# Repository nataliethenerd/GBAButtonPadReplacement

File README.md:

# GBA Button Pad Replacement

Open source replacement PCBs for the Game Boy Advance button contacts. Order as a flex PCB and solder to the test points (or traces if the test points are dead also). [Check out my GBA scans if you need help locating the traces](https://wiki.nataliethenerd.com/gameboy/gameboyadvance#agb-cpu-01)

## Follow me

If you are into Game Boy modding or retro gaming, please consider using code "NatalieTheNerd" at:

• [Retro Modding](http://RetroModding.com) 

• [Retro Game Repair Shop](http://RetroGameRepairShop.com) 

• [Extreme Rate](http://ExtremeRate.com)

**My socials**

• [Twitter](https://twitter.com/natalie_thenerd) 

• [BlueSky](https://bsky.app/profile/nataliethenerd.com) 

• [Instagram](https://www.instagram.com/natalie.thenerd/) 

• [Modded Gameboy Club](https://moddedgameboy.club/) - a club dedicated to the modification of Game Boys, freely sharing resources

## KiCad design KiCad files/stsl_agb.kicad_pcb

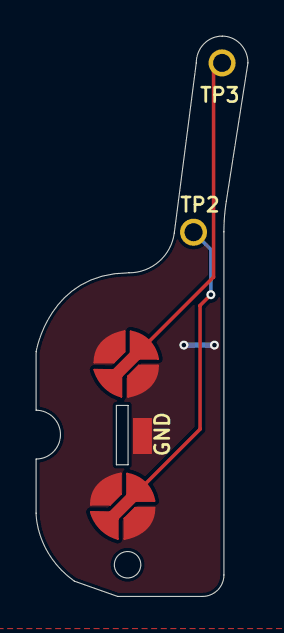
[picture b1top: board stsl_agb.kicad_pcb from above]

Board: 2 copper layers, 11.7 x 31.1 mm, 5 parts (0 on the bottom side), 3 nets.

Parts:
GND: TestPoint; TestPoint_Pad_2.0x2.0mm
SW5: START; AGB ST SL
SW6: SELECT; AGB ST SL
TP2, TP3: TestPoint; TESTPAD

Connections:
GND: GND.1, SW5.2, SW6.2
unnamed: SW5.1, TP3.1
unnamed: SW6.1, TP2.1

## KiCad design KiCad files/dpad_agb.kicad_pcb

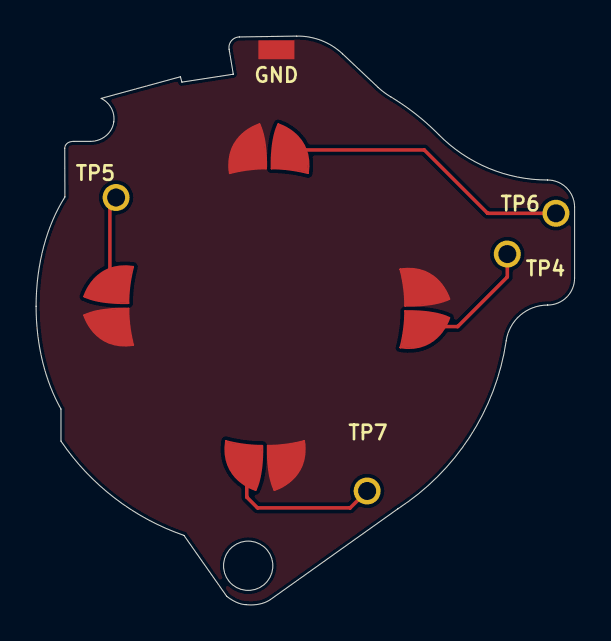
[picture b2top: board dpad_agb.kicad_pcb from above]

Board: 2 copper layers, 29.9 x 31.6 mm, 9 parts (0 on the bottom side), 5 nets.

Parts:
GND: TestPoint; TestPoint_Pad_2.0x2.0mm
SW1: UP; ABG DPAD
SW2: LEFT; ABG DPAD
SW3: DOWN; ABG DPAD
SW4: RIGHT; ABG DPAD
TP4, TP5, TP6, TP7: TestPoint; TESTPAD

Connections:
GND: GND.1, SW1.1, SW2.1, SW3.1, SW4.1
unnamed: SW1.2, TP6.1
unnamed: SW2.2, TP5.1
unnamed: SW3.2, TP7.1
unnamed: SW4.2, TP4.1

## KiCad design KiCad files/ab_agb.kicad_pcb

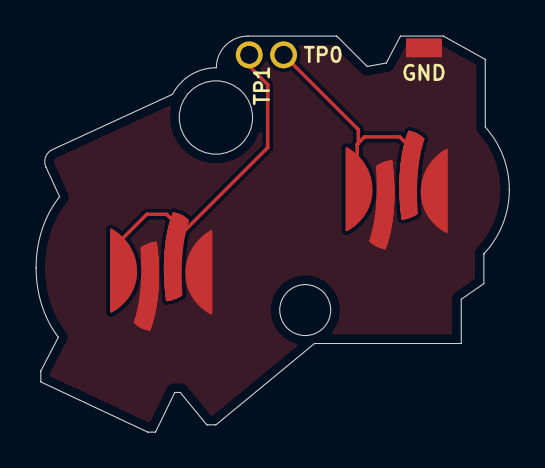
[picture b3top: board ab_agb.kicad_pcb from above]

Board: 2 copper layers, 26.3 x 22.0 mm, 5 parts (0 on the bottom side), 3 nets.

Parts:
GND: TestPoint; TestPoint_Pad_2.0x2.0mm
SW7: A; AGB AB
SW8: B; AGB AB
TP0, TP1: TestPoint; TESTPAD

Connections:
GND: GND.1, SW7.1, SW8.1
unnamed: SW7.2, TP0.1
unnamed: SW8.2, TP1.1

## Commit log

2026-01-16 first
2026-01-16 read me and license added
